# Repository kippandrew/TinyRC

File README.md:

TinyRC
==============

About
-----
The TinyRC is a open source hardware device for
converting servo signals from RC receivers (such as the Spektrum
AR6210) into a TTL serial stream that can be read by a microcontroller
such as an Arduino. 

The TinyRC works by timing the pulses received on up to
6 channels, and using an ATTiny84 microcontroller to convert those
pulses into a serial packet stream.

Hardware
--------
The TinyRC uses an ATTiny84 microcontroller from
Atmel. The board features and ISCP programming header, decoupling caps
and power indicator LED.

The board accepts a +5V source, and can provide power to the receiver. 

### Components ###

<table>
    <tr>
        <th>Part</th>
        <th>Description</th>
        <th>Part Number</th>
    </tr>
    <tr>
        <td>IC1</td>
        <td>Atmel ATTINY84A-SSU 14-SOIC SMD</td>
        <td>DigiKey P/N: <a href="http://www.digikey.com/product-detail/en/ATTINY84A-SSU/ATTINY84A-SSU-ND/3046522">ATTINY84A-SSU-ND</a></td>
    </tr>
    <tr>
        <td>C1</td>
        <td>Capcaitor 0.1uF</td>
        <td>DigiKey P/N: <a href="http://www.digikey.com/product-detail/en/C315C104M5U5TA/399-4151-ND/817927">399-4151-ND</a></td>
    </tr>
    <tr>
        <td>C2,C3</td>
        <td>CAP CER 22PF 50V 5% SMD 0805</td>
        <td>DigiKey P/N: <a href="http://www.digikey.com/product-detail/en/CC0805JRNPO9BN220/311-1103-1-ND/303013">311-1103-1-ND</a></td>
    </tr>
    <tr>
        <td>Y1</td>
        <td>CRYSTAL 20.0MHZ 50PF THRU</td>
        <td>DigiKey P/N: <a href="http://www.digikey.com/product-detail/en/ATS20B/CTX1108-ND/2640039">CTX1108-ND</a></td>
    </tr>
    <tr>
        <td>D1</td>
        <td>Diode SOD-323 SMD</td>
        <td>DigiKey P/N: <a href="http://www.digikey.com/product-detail/en/BAS316,115/568-5003-1-ND/2209919">568-5003-1-ND</a></td>
    </tr>
    <tr>
        <td>R1</td>
        <td>RES 330 OHM 5% 0805</td>
        <td>DigiKey P/N: <a href="http://www.digikey.com/product-detail/en/ERJ-P06J331V/P330ADCT-ND/525496">P330ADCT-ND</a></td>
    </tr>
    <tr>
        <td>LED1</td>
        <td>LED Red 1206 SMD</td>
        <td>DigiKey P/N: <a href="http://www.digikey.com/product-detail/en/LTST-C150CKT/160-1167-1-ND/269239">160-1167-1-ND</a></td>
    </tr>
    <tr>
        <td>JP1</td>
        <td>0.1" pitch Header 2x5</td>
        <td>DigiKey P/N: <a href="http://www.digikey.com/product-detail/en/67997-410HLF/609-3243-ND/1878475">609-3243-ND</a></td>
    </tr>
    <tr>
        <td>JP2</td>
        <td>0.1" pitch Header 2x3</td>
        <td>DigiKey P/N: <a href="http://www.digikey.com/product-detail/en/77313-422R06LF/609-4517-ND/2665635">609-4517-ND</a></td>
    </tr>
    <tr>
        <td>JP3</td>
        <td>0.1" pitch Header 1x3</td>
        <td>DigiKey P/N: <a href="http://www.digikey.com/product-detail/en/68000-103HLF/609-3461-ND/2023309">609-3461-ND</a></Otd>
    </tr>
</table>

Software
--------

The TinyRC runs and ATTINY Arduino core
(instructions on how to use the ATTINY Arduino core can be found
[here](http://hlt.media.mit.edu/?p=1695)). To program the board you
will need and AVR ISP programmer such as the [Pocket AVR
Programmer](https://www.sparkfun.com/products/9825) from SparkFun. It
is also possible to using a standard Arduino as an ISP programmer.

When programming the TinyRC for the first time, be
sure to burn the bootloader, and set the fuse bits for 8Mhz clock. The
default for the ATTiny84 is 1Mhz.

Instructions
------------

By default the TinyRC will output a 17 byte serial
packet every 100ms. The first 4 bytes are a header used to identify
the start of the packet. The packet header is 4 bytes with a value 0xFF.
Following the packet header is 1 byte of receiver status. This is currently
unused. Each channel follows the packet header encoded in two bytes.

Example Packet:

    --------------------------------------------------------------------------------------------------------------------------------------------
    | header (4 bytes)       | Status (1 byte) | CH1 (2 bytes) | CH2 (2 bytes) | CH3 (2 bytes) | CH4 (2 bytes) | CH5 (2 bytes) | CH6 (2 bytes) |
    --------------------------------------------------------------------------------------------------------------------------------------------
    | 0xFF, 0xFF, 0xFF, 0xFF | 0x00            | 0x00, 0x01    | 0x02, 0x03    | 0x04, 0x05    | 0x06, 0x07    | 0x06, 0x07    | 0x08, 0x0A    |
    --------------------------------------------------------------------------------------------------------------------------------------------

Example reading the packet from Arduino (Mega):

    uint8_t packetHeader[4] = {
      0xFF, 0xFF, 0xFF, 0xFF};

    void setup() {
      // initialize serial
      Serial.begin(115200); 
      Serial1.begin(9600);
    }

    boolean readPacketHeader(uint8_t *header, size_t headerLength, uint32_t timeout) {
      byte index = 0;
      byte b = 0;
      uint32_t startTime = millis();
      while (millis() - startTime < timeout) {
        if (index >= headerLength) {
          return true;
        }
        if (Serial1.available() > 0) {
          b = Serial1.read();
          if (b == header[index]) {
            index++;
          } 
          else {
            index = 0;
          }
        }
      }
      // timeout
      return false;
    }

    void loop() {
      static uint16_t channels[6];
      byte len;
      uint8_t buf[2];
      uint8_t status;

      if (readPacketHeader(packetHeader, 4, 10)) {
        status = Serial1.read();
        // for each channel
        for (int ch = 0; ch < 6; ch++) {
          // Read two bytes
          len = Serial1.readBytes((char*)buf, 2);
          if (len >= 2) {
            memcpy(&channels[ch], buf, sizeof(uint16_t));
          }
        }
      }
      
      for (int ch = 0; ch < 6; ch++) {
        Serial.print("ch ");
        Serial.print(ch + 1, DEC);
        Serial.print(" ");
        Serial.print(channels[ch]);
        Serial.print(" ");
      }
      
      Serial.println();

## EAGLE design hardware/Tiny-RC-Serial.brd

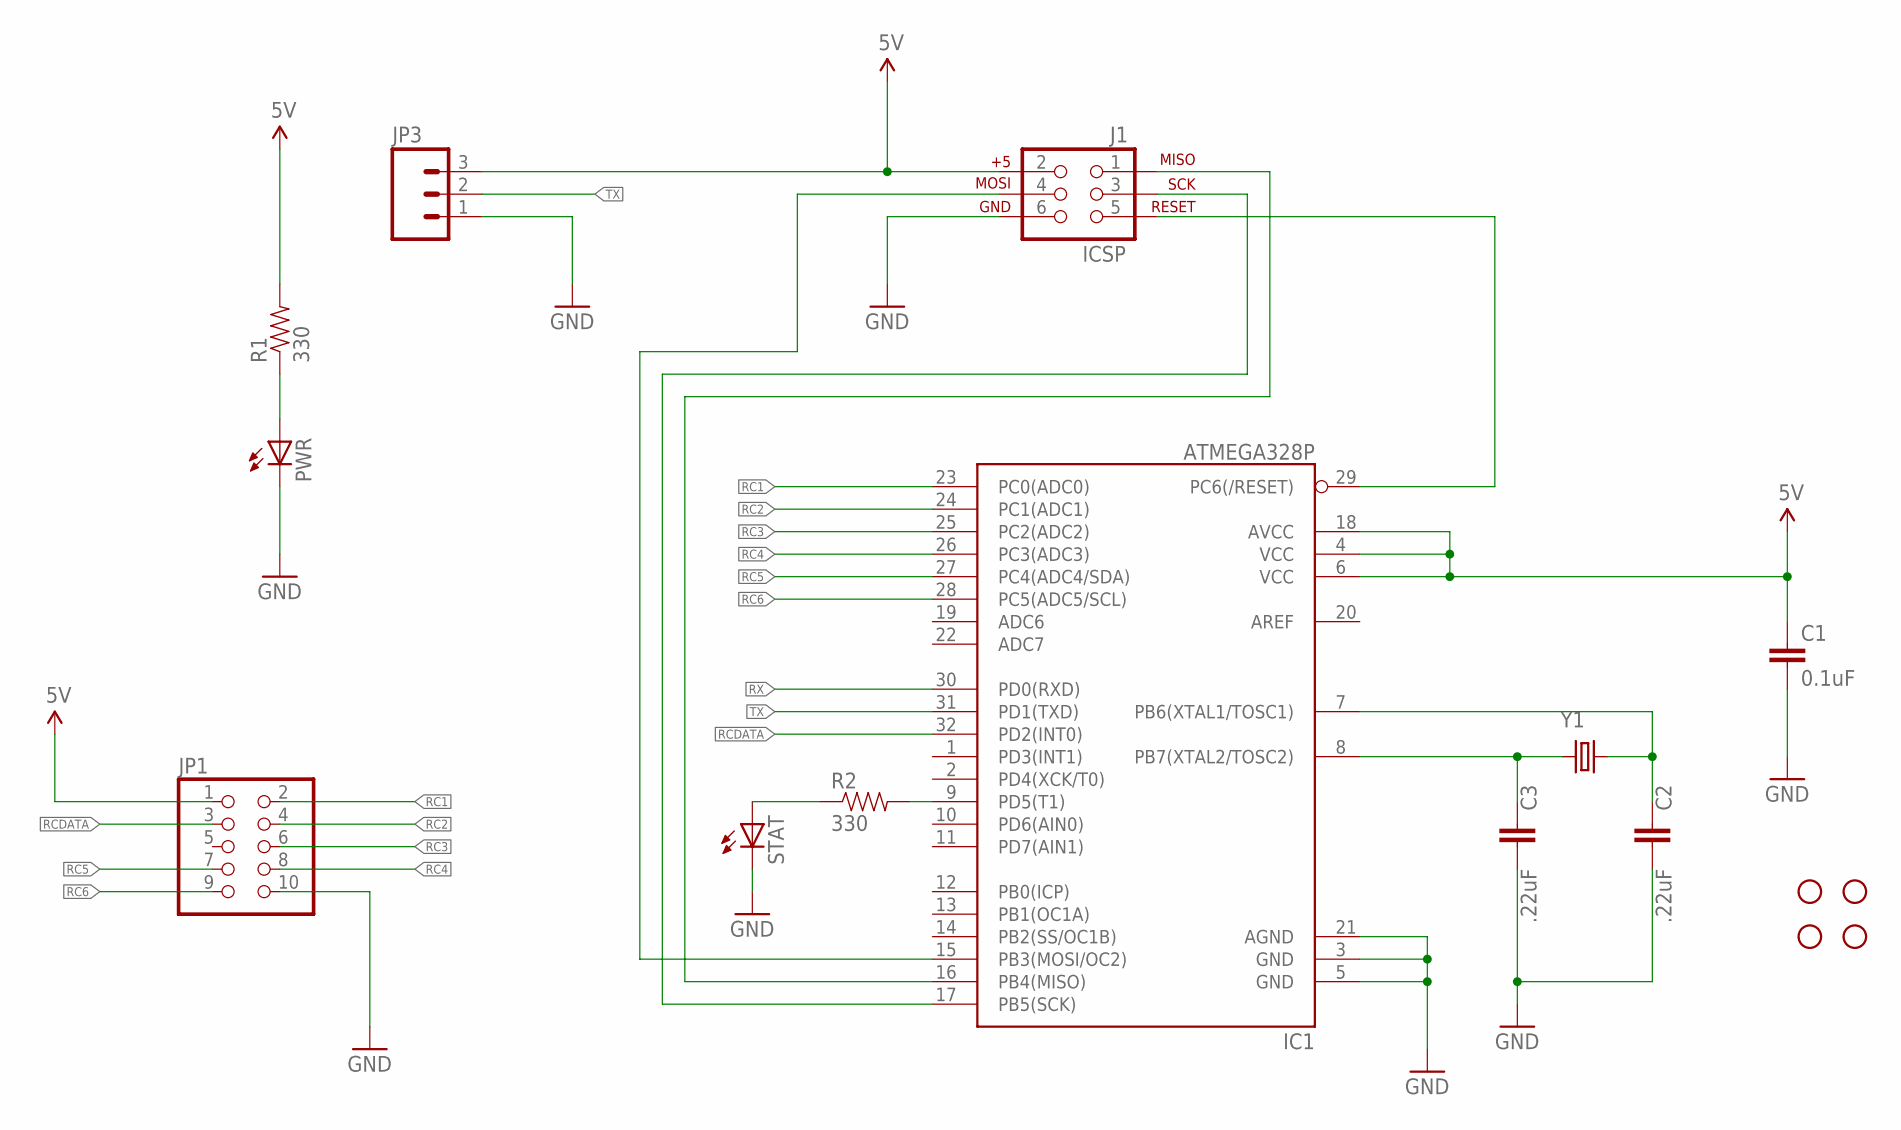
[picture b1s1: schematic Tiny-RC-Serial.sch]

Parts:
C1: 0.1uF; CAP-PTH-SMALL-KIT
C2, C3: .22uF; CAP-PTH-SMALL-KIT
IC1: ATMEGA328P; TQFP32-08
J1: ICSP; 2X3
JP1: PINHD-2X5; 2X05
JP3: M03PTH; 1X03
PWR: LED1206; LED-1206
R1, R2: 330; 1206
S1, S2, S3, S4: STAND-OFFTIGHT; STAND-OFF-TIGHT
STAT: LED1206; LED-1206
Y1: 20Mhz; HC49US

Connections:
5V: C1.1, IC1.4 (VCC), IC1.6 (VCC), IC1.18 (AVCC), J1.2, JP1.1, JP3.3, R1.2
GND: C1.2, C2.2, C3.2, IC1.3 (GND), IC1.5 (GND), IC1.21 (AGND), J1.6, JP1.10, JP3.1, PWR.C, STAT.C
MISO: IC1.16 (PB4(MISO)), J1.1
MOSI: IC1.15 (PB3(MOSI/OC2)), J1.4
unnamed: IC1.9 (PD5(T1)), R2.2
unnamed: PWR.A, R1.1
unnamed: C2.1, IC1.7 (PB6(XTAL1/TOSC1)), Y1.2
unnamed: C3.1, IC1.8 (PB7(XTAL2/TOSC2)), Y1.1
unnamed: R2.1, STAT.A
RC1: IC1.23 (PC0(ADC0)), JP1.2
RC2: IC1.24 (PC1(ADC1)), JP1.4
RC3: IC1.25 (PC2(ADC2)), JP1.6
RC4: IC1.26 (PC3(ADC3)), JP1.8
RC5: IC1.27 (PC4(ADC4/SDA)), JP1.7
RC6: IC1.28 (PC5(ADC5/SCL)), JP1.9
RCDATA: IC1.32 (PD2(INT0)), JP1.3
RESET: IC1.29 (PC6(/RESET)), J1.5
RX: IC1.30 (PD0(RXD))
SCK: IC1.17 (PB5(SCK)), J1.3
TX: IC1.31 (PD1(TXD)), JP3.2

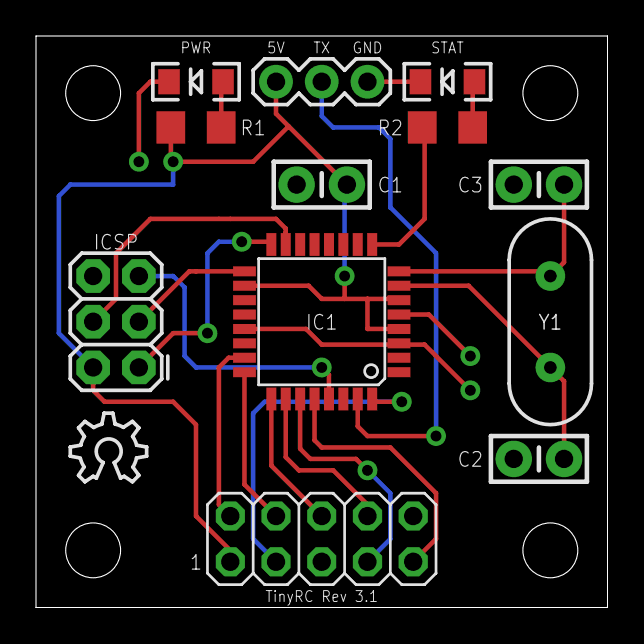
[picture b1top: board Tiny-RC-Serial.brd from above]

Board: 2 copper layers, 31.8 x 31.8 mm, 17 parts (0 on the bottom side), 19 nets.

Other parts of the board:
U$5: OSHW_8X150_NOTEXT

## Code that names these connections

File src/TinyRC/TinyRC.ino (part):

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// Reference: ATMEL ATMEGA328
//
//                           +-\/-+
//             RESET  PC6   1|    |28  PC5  (A 5)
//         (D 0) RX   PD0   2|    |27  PC4  (A 4)
//         (D 1) TX   PD1   3|    |26  PC3  (A 3)
//             (D 2)  PD2   4|    |25  PC2  (A 2)
//             (D 3)  PD3   5|    |24  PC1  (A 1)
//             (D 4)  PD4   6|    |23  PC0  (A 0)
//                    VCC   7|    |22  GND
//                    GND   8|    |21  AREF
//             XTAL1  PB6   9|    |20  AVCC (A 0)
//             XTAL2  PB7  10|    |19  PB5  (D 13)
//             (D 5)  PD5  11|    |18  PB4  (D 12)
//             (D 6)  PD6  12|    |17  PB3  (D 11)
//             (D 7)  PD7  13|    |16  PB2  (D 10)
//             (D 8)  PD0  14|    |15  PB1  (D 9)
//                           +----+
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#define RECEIVER_CH5 4
#define RECEIVER_CH6 5

#define RECEIVER_CH1_IN_PIN 0  // PC0 / A0 / PCINT8
#define RECEIVER_CH2_IN_PIN 1  // PC1 / A1 / PCINT9
#define RECEIVER_CH3_IN_PIN 2  // PC2 / A2 / PCINT10
#define RECEIVER_CH4_IN_PIN 3  // PC3 / A3 / PCINT11
#define RECEIVER_CH5_IN_PIN 4  // PC4 / A4 / PCINT12
#define RECEIVER_CH6_IN_PIN 5  // PC5 / A5 / PCINT13

#define RECEIVER_CH1_FLAG 1
#define RECEIVER_CH2_FLAG 2
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
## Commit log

2012-12-30 intial commit
2012-12-30 added software serial library
2012-12-30 more readme updates
2012-12-30 added images
2012-12-30 added image to readme
2012-12-30 updated readme and sch and brd
2013-02-16 organized code files
2013-02-16 updated to version 3.0
2013-02-16 updated ignore
2013-02-16 updated readme with 3.0 parts
2013-02-16 updated images
2013-02-16 updated rinyrc board
2013-02-16 removed values
2013-02-16 added OSH park zip
2013-02-19 updated tinyRC code with watchdog timer
2013-02-24 removed whitespace
2013-02-24 updated board to rev 3.0 - now using ATTiny2313
2013-10-20 Initial port to AtMega328

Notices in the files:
src/TinyRC/TinyRC.ino:
Copyright (C) 2012-2013 Andy Kipp <kipp.andrew@gmail.com>
hardware/Tiny-RC-Serial.brd:
(c) 2013 Andy Kipp
parts and their libraries:
SparkFun: Licensing: CC v3.0 Share-Alike You are welcome to use this library for commercial purposes.
